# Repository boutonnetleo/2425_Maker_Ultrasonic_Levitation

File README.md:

# 2425_Maker_Ultrasonic_Levitation
Ultrasonic levitation using phased array

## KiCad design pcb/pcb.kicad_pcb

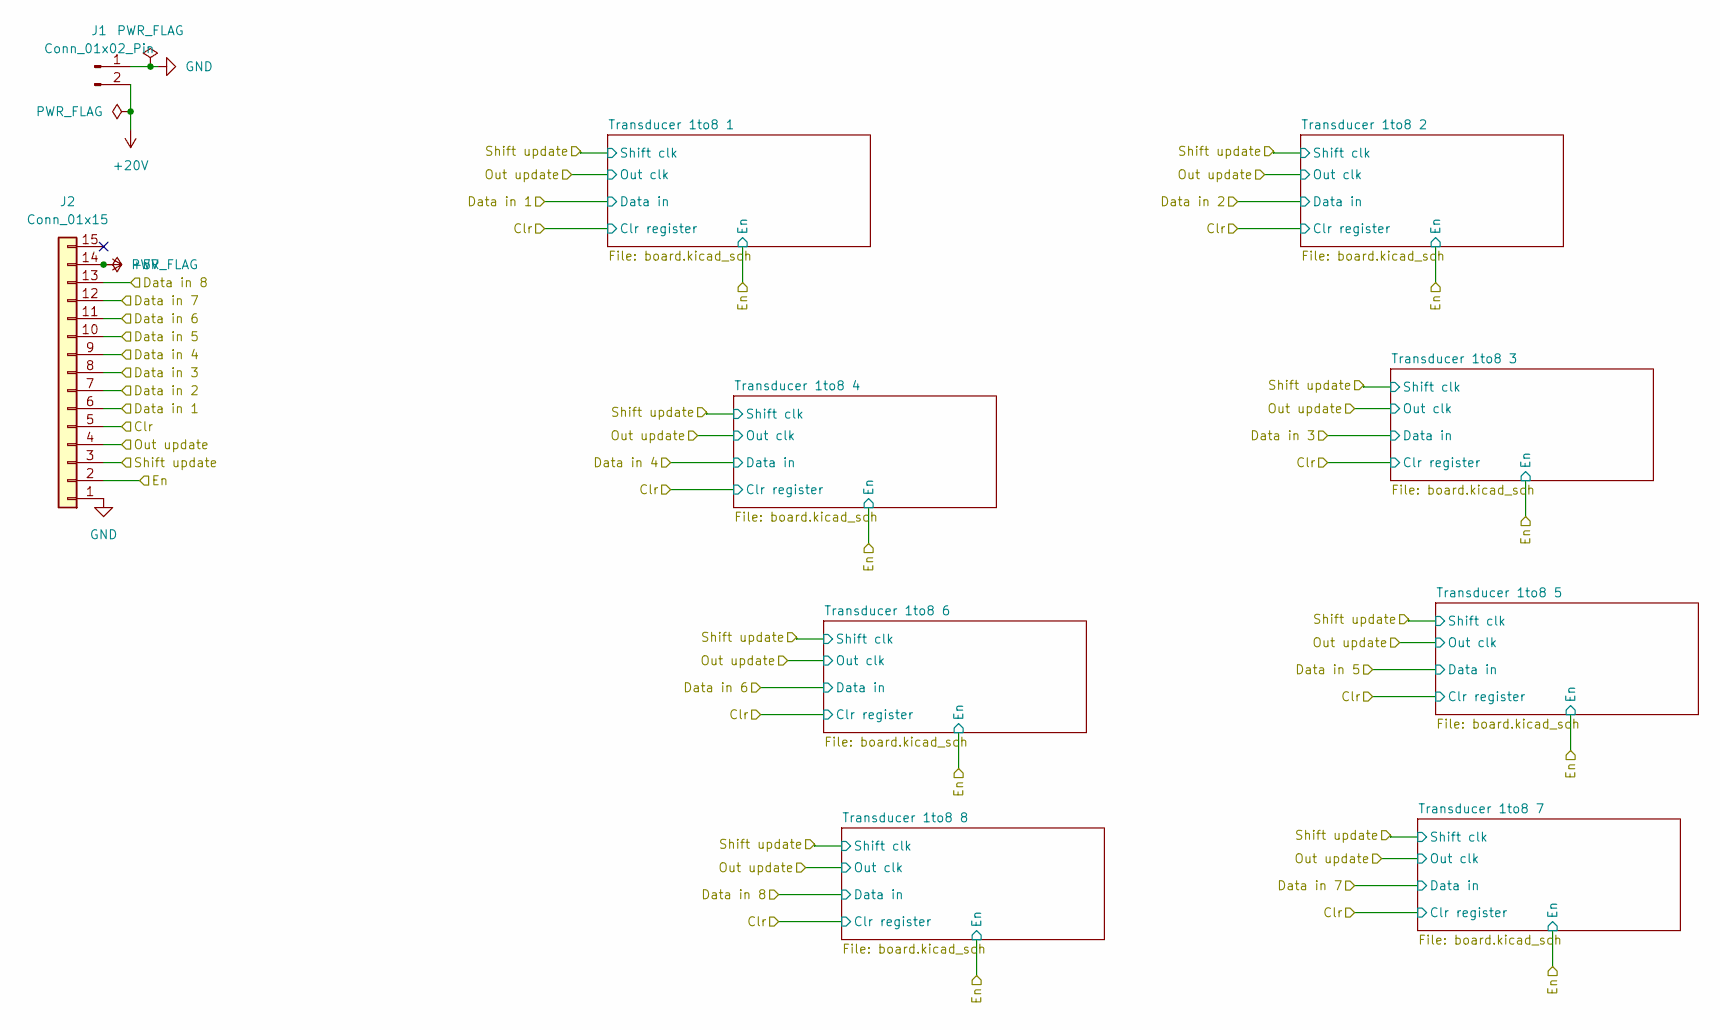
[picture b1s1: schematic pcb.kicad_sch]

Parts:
J1: Conn_01x02_Pin; AMASS_XT30UPB-F_1x02_P5.0mm_Vertical; JLCPCB C428721
J2: Conn_01x15; PinHeader_1x15_P2.54mm_Vertical; JLCPCB C7509525

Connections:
+5V: J2.14; also elsewhere on the board
+20V: J1.2; also elsewhere on the board
/Clr: J2.5; also elsewhere on the board
/Data in 1: J2.6; also elsewhere on the board
/Data in 2: J2.7; also elsewhere on the board
/Data in 3: J2.8; also elsewhere on the board
/Data in 4: J2.9; also elsewhere on the board
/Data in 5: J2.10; also elsewhere on the board
/Data in 6: J2.11; also elsewhere on the board
/Data in 7: J2.12; also elsewhere on the board
/Data in 8: J2.13; also elsewhere on the board
/En: J2.2; also elsewhere on the board
/Out update: J2.4; also elsewhere on the board
/Shift update: J2.3; also elsewhere on the board
GND: J1.1, J2.1; also elsewhere on the board

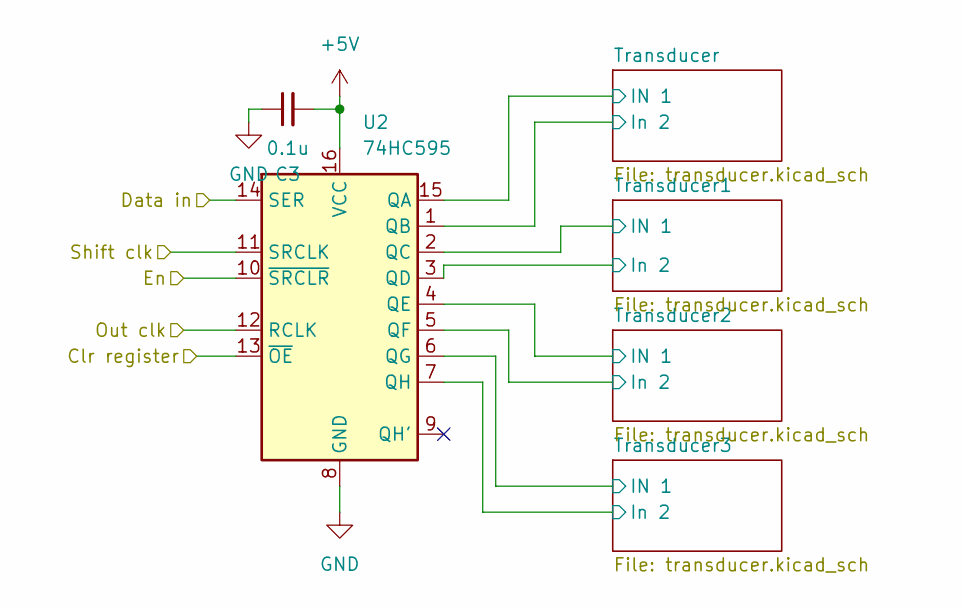
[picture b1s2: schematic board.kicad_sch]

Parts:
C3: 0.1u; C_0201_0603Metric; JLCPCB C386070
U2: 74HC595; SOIC-16_3.9x9.9mm_P1.27mm; JLCPCB C5947

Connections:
+5V: C3.2, U2.16 (VCC); also elsewhere on the board
/Clr: U2.13 (~OE); also elsewhere on the board
/Data in 1: U2.14 (SER); also elsewhere on the board
/En: U2.10 (~SRCLR); also elsewhere on the board
/Out update: U2.12 (RCLK); also elsewhere on the board
/Shift update: U2.11 (SRCLK); also elsewhere on the board
/Transducer 1to8 1/Transducer1/IN 1: U2.2 (QC); also elsewhere on the board
/Transducer 1to8 1/Transducer1/In 2: U2.3 (QD); also elsewhere on the board
/Transducer 1to8 1/Transducer2/IN 1: U2.4 (QE); also elsewhere on the board
/Transducer 1to8 1/Transducer2/In 2: U2.5 (QF); also elsewhere on the board
/Transducer 1to8 1/Transducer3/IN 1: U2.6 (QG); also elsewhere on the board
/Transducer 1to8 1/Transducer3/In 2: U2.7 (QH); also elsewhere on the board
/Transducer 1to8 1/Transducer/IN 1: U2.15 (QA); also elsewhere on the board
/Transducer 1to8 1/Transducer/In 2: U2.1 (QB); also elsewhere on the board
GND: C3.1, U2.8 (GND); also elsewhere on the board

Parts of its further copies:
C10, C19, C28, C37, C46, C55, C64: 0.1u; C_0201_0603Metric; JLCPCB C386070
U6, U11, U16, U21, U26, U31, U36: 74HC595; SOIC-16_3.9x9.9mm_P1.27mm; JLCPCB C5947

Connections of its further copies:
+5V: C10.2, C19.2, C28.2, C37.2, C46.2, C55.2, C64.2, U6.16 (VCC), U11.16 (VCC), U16.16 (VCC), U21.16 (VCC), U26.16 (VCC), U31.16 (VCC), U36.16 (VCC); also elsewhere on the board
/Clr: U6.13 (~OE), U11.13 (~OE), U16.13 (~OE), U21.13 (~OE), U26.13 (~OE), U31.13 (~OE), U36.13 (~OE); also elsewhere on the board
/Data in 2: U6.14 (SER); also elsewhere on the board
/Data in 3: U11.14 (SER); also elsewhere on the board
/Data in 4: U16.14 (SER); also elsewhere on the board
/Data in 5: U21.14 (SER); also elsewhere on the board
/Data in 6: U26.14 (SER); also elsewhere on the board
/Data in 7: U31.14 (SER); also elsewhere on the board
/Data in 8: U36.14 (SER); also elsewhere on the board
/En: U6.10 (~SRCLR), U11.10 (~SRCLR), U16.10 (~SRCLR), U21.10 (~SRCLR), U26.10 (~SRCLR), U31.10 (~SRCLR), U36.10 (~SRCLR); also elsewhere on the board
/Out update: U6.12 (RCLK), U11.12 (RCLK), U16.12 (RCLK), U21.12 (RCLK), U26.12 (RCLK), U31.12 (RCLK), U36.12 (RCLK); also elsewhere on the board
/Shift update: U6.11 (SRCLK), U11.11 (SRCLK), U16.11 (SRCLK), U21.11 (SRCLK), U26.11 (SRCLK), U31.11 (SRCLK), U36.11 (SRCLK); also elsewhere on the board
/Transducer 1to8 2/Transducer1/IN 1: U6.2 (QC); also elsewhere on the board
/Transducer 1to8 2/Transducer1/In 2: U6.3 (QD); also elsewhere on the board
/Transducer 1to8 2/Transducer2/IN 1: U6.4 (QE); also elsewhere on the board
/Transducer 1to8 2/Transducer2/In 2: U6.5 (QF); also elsewhere on the board
/Transducer 1to8 2/Transducer3/IN 1: U6.6 (QG); also elsewhere on the board
/Transducer 1to8 2/Transducer3/In 2: U6.7 (QH); also elsewhere on the board
/Transducer 1to8 2/Transducer/IN 1: U6.15 (QA); also elsewhere on the board
/Transducer 1to8 2/Transducer/In 2: U6.1 (QB); also elsewhere on the board
/Transducer 1to8 3/Transducer1/IN 1: U11.2 (QC); also elsewhere on the board
/Transducer 1to8 3/Transducer1/In 2: U11.3 (QD); also elsewhere on the board
/Transducer 1to8 3/Transducer2/IN 1: U11.4 (QE); also elsewhere on the board
/Transducer 1to8 3/Transducer2/In 2: U11.5 (QF); also elsewhere on the board
/Transducer 1to8 3/Transducer3/IN 1: U11.6 (QG); also elsewhere on the board
/Transducer 1to8 3/Transducer3/In 2: U11.7 (QH); also elsewhere on the board
/Transducer 1to8 3/Transducer/IN 1: U11.15 (QA); also elsewhere on the board
/Transducer 1to8 3/Transducer/In 2: U11.1 (QB); also elsewhere on the board
/Transducer 1to8 4/Transducer1/IN 1: U16.2 (QC); also elsewhere on the board
/Transducer 1to8 4/Transducer1/In 2: U16.3 (QD); also elsewhere on the board
/Transducer 1to8 4/Transducer2/IN 1: U16.4 (QE); also elsewhere on the board
/Transducer 1to8 4/Transducer2/In 2: U16.5 (QF); also elsewhere on the board
/Transducer 1to8 4/Transducer3/IN 1: U16.6 (QG); also elsewhere on the board
/Transducer 1to8 4/Transducer3/In 2: U16.7 (QH); also elsewhere on the board
/Transducer 1to8 4/Transducer/IN 1: U16.15 (QA); also elsewhere on the board
/Transducer 1to8 4/Transducer/In 2: U16.1 (QB); also elsewhere on the board
/Transducer 1to8 5/Transducer1/IN 1: U21.2 (QC); also elsewhere on the board
/Transducer 1to8 5/Transducer1/In 2: U21.3 (QD); also elsewhere on the board
/Transducer 1to8 5/Transducer2/IN 1: U21.4 (QE); also elsewhere on the board
/Transducer 1to8 5/Transducer2/In 2: U21.5 (QF); also elsewhere on the board
/Transducer 1to8 5/Transducer3/IN 1: U21.6 (QG); also elsewhere on the board
/Transducer 1to8 5/Transducer3/In 2: U21.7 (QH); also elsewhere on the board
/Transducer 1to8 5/Transducer/IN 1: U21.15 (QA); also elsewhere on the board
/Transducer 1to8 5/Transducer/In 2: U21.1 (QB); also elsewhere on the board
/Transducer 1to8 6/Transducer1/IN 1: U26.2 (QC); also elsewhere on the board
/Transducer 1to8 6/Transducer1/In 2: U26.3 (QD); also elsewhere on the board
/Transducer 1to8 6/Transducer2/IN 1: U26.4 (QE); also elsewhere on the board
/Transducer 1to8 6/Transducer2/In 2: U26.5 (QF); also elsewhere on the board
/Transducer 1to8 6/Transducer3/IN 1: U26.6 (QG); also elsewhere on the board
/Transducer 1to8 6/Transducer3/In 2: U26.7 (QH); also elsewhere on the board
/Transducer 1to8 6/Transducer/IN 1: U26.15 (QA); also elsewhere on the board
/Transducer 1to8 6/Transducer/In 2: U26.1 (QB); also elsewhere on the board
/Transducer 1to8 7/Transducer1/IN 1: U31.2 (QC); also elsewhere on the board
/Transducer 1to8 7/Transducer1/In 2: U31.3 (QD); also elsewhere on the board
/Transducer 1to8 7/Transducer2/IN 1: U31.4 (QE); also elsewhere on the board
/Transducer 1to8 7/Transducer2/In 2: U31.5 (QF); also elsewhere on the board
/Transducer 1to8 7/Transducer3/IN 1: U31.6 (QG); also elsewhere on the board
/Transducer 1to8 7/Transducer3/In 2: U31.7 (QH); also elsewhere on the board
/Transducer 1to8 7/Transducer/IN 1: U31.15 (QA); also elsewhere on the board
/Transducer 1to8 7/Transducer/In 2: U31.1 (QB); also elsewhere on the board
/Transducer 1to8 8/Transducer1/IN 1: U36.2 (QC); also elsewhere on the board
/Transducer 1to8 8/Transducer1/In 2: U36.3 (QD); also elsewhere on the board
/Transducer 1to8 8/Transducer2/IN 1: U36.4 (QE); also elsewhere on the board
/Transducer 1to8 8/Transducer2/In 2: U36.5 (QF); also elsewhere on the board
/Transducer 1to8 8/Transducer3/IN 1: U36.6 (QG); also elsewhere on the board
/Transducer 1to8 8/Transducer3/In 2: U36.7 (QH); also elsewhere on the board
/Transducer 1to8 8/Transducer/IN 1: U36.15 (QA); also elsewhere on the board
/Transducer 1to8 8/Transducer/In 2: U36.1 (QB); also elsewhere on the board
GND: C10.1, C19.1, C28.1, C37.1, C46.1, C55.1, C64.1, U6.8 (GND), U11.8 (GND), U16.8 (GND), U21.8 (GND), U26.8 (GND), U31.8 (GND), U36.8 (GND); also elsewhere on the board

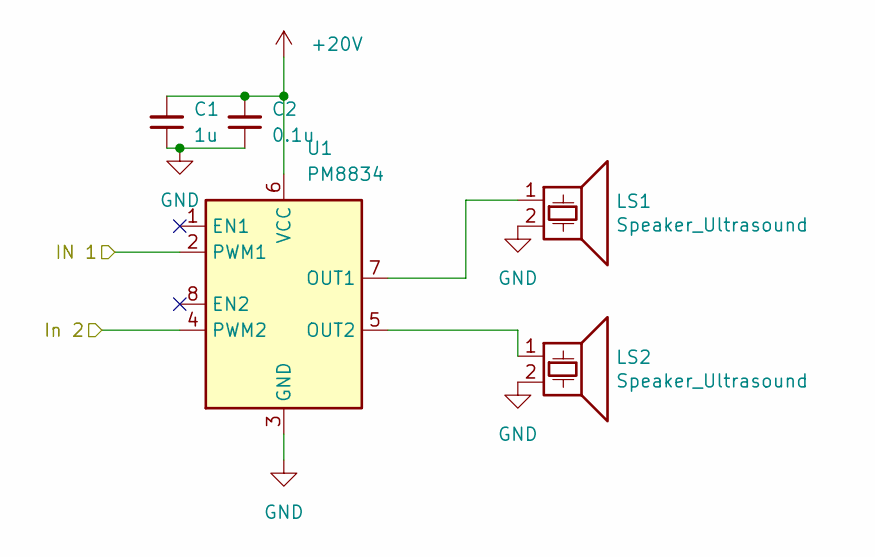
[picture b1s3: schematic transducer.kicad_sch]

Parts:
C1: 1u; C_0402_1005Metric; JLCPCB C52923
C2: 0.1u; C_0201_0603Metric; JLCPCB C386070
LS1, LS2: Speaker_Ultrasound; MSO-P1040H07T
U1: PM8834; SOIC-8_3.9x4.9mm_P1.27mm; JLCPCB C465729

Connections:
+20V: C1.2, C2.2, U1.6 (VCC); also elsewhere on the board
/Transducer 1to8 1/Transducer/IN 1: U1.2 (PWM1); also elsewhere on the board
/Transducer 1to8 1/Transducer/In 2: U1.4 (PWM2); also elsewhere on the board
GND: C1.1, C2.1, LS1.2, LS2.2, U1.3 (GND); also elsewhere on the board
unnamed: LS1.1, U1.7 (OUT1)
unnamed: LS2.1, U1.5 (OUT2)

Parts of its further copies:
C4, C6, C8, C11, C13, C15, C17, C20, C22, C24, C26, C29, C31, C33, C35, C38, C40, C42, C44, C47, C49, C51, C53, C56, C58, C60, C62, C65, C67, C69, C71: 1u; C_0402_1005Metric; JLCPCB C52923
C5, C7, C9, C12, C14, C16, C18, C21, C23, C25, C27, C30, C32, C34, C36, C39, C41, C43, C45, C48, C50, C52, C54, C57, C59, C61, C63, C66, C68, C70, C72: 0.1u; C_0201_0603Metric; JLCPCB C386070
LS3, LS4, LS5, LS6, LS7, LS8, LS9, LS10, LS11, LS12, LS13, LS14, LS15, LS16, LS17, LS18, LS19, LS20, LS21, LS22, LS23, LS24, LS25, LS26, LS27, LS28, LS29, LS30, LS31, LS32, LS33, LS34, LS35, LS36, LS37, LS38, LS39, LS40, LS41, LS42, LS43, LS44, LS45, LS46, LS47, LS48, LS49, LS50, LS51, LS52, LS53, LS54, LS55, LS56, LS57, LS58, LS59, LS60, LS61, LS62, LS63, LS64: Speaker_Ultrasound; MSO-P1040H07T
U3, U4, U5, U7, U8, U9, U10, U12, U13, U14, U15, U17, U18, U19, U20, U22, U23, U24, U25, U27, U28, U29, U30, U32, U33, U34, U35, U37, U38, U39, U40: PM8834; SOIC-8_3.9x4.9mm_P1.27mm; JLCPCB C465729

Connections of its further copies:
+20V: C4.2, C5.2, C6.2, C7.2, C8.2, C9.2, C11.2, C12.2, C13.2, C14.2, C15.2, C16.2, C17.2, C18.2, C20.2, C21.2, C22.2, C23.2, C24.2, C25.2, C26.2, C27.2, C29.2, C30.2, C31.2, C32.2, C33.2, C34.2, C35.2, C36.2, C38.2, C39.2, C40.2, C41.2, C42.2, C43.2, C44.2, C45.2, C47.2, C48.2, C49.2, C50.2, C51.2, C52.2, C53.2, C54.2, C56.2, C57.2, C58.2, C59.2, C60.2, C61.2, C62.2, C63.2, C65.2, C66.2, C67.2, C68.2, C69.2, C70.2, C71.2, C72.2, U3.6 (VCC), U4.6 (VCC), U5.6 (VCC), U7.6 (VCC), U8.6 (VCC), U9.6 (VCC), U10.6 (VCC), U12.6 (VCC), U13.6 (VCC), U14.6 (VCC), U15.6 (VCC), U17.6 (VCC), U18.6 (VCC), U19.6 (VCC), U20.6 (VCC), U22.6 (VCC), U23.6 (VCC), U24.6 (VCC), U25.6 (VCC), U27.6 (VCC), U28.6 (VCC), U29.6 (VCC), U30.6 (VCC), U32.6 (VCC), U33.6 (VCC), U34.6 (VCC), U35.6 (VCC), U37.6 (VCC), U38.6 (VCC), U39.6 (VCC), U40.6 (VCC); also elsewhere on the board
/Transducer 1to8 1/Transducer1/IN 1: U3.2 (PWM1); also elsewhere on the board
/Transducer 1to8 1/Transducer1/In 2: U3.4 (PWM2); also elsewhere on the board
/Transducer 1to8 1/Transducer2/IN 1: U4.2 (PWM1); also elsewhere on the board
/Transducer 1to8 1/Transducer2/In 2: U4.4 (PWM2); also elsewhere on the board
/Transducer 1to8 1/Transducer3/IN 1: U5.2 (PWM1); also elsewhere on the board
/Transducer 1to8 1/Transducer3/In 2: U5.4 (PWM2); also elsewhere on the board
/Transducer 1to8 2/Transducer1/IN 1: U9.2 (PWM1); also elsewhere on the board
/Transducer 1to8 2/Transducer1/In 2: U9.4 (PWM2); also elsewhere on the board
/Transducer 1to8 2/Transducer2/IN 1: U8.2 (PWM1); also elsewhere on the board
/Transducer 1to8 2/Transducer2/In 2: U8.4 (PWM2); also elsewhere on the board
/Transducer 1to8 2/Transducer3/IN 1: U7.2 (PWM1); also elsewhere on the board
/Transducer 1to8 2/Transducer3/In 2: U7.4 (PWM2); also elsewhere on the board
/Transducer 1to8 2/Transducer/IN 1: U10.2 (PWM1); also elsewhere on the board
/Transducer 1to8 2/Transducer/In 2: U10.4 (PWM2); also elsewhere on the board
/Transducer 1to8 3/Transducer1/IN 1: U14.2 (PWM1); also elsewhere on the board
/Transducer 1to8 3/Transducer1/In 2: U14.4 (PWM2); also elsewhere on the board
/Transducer 1to8 3/Transducer2/IN 1: U13.2 (PWM1); also elsewhere on the board
/Transducer 1to8 3/Transducer2/In 2: U13.4 (PWM2); also elsewhere on the board
/Transducer 1to8 3/Transducer3/IN 1: U12.2 (PWM1); also elsewhere on the board
/Transducer 1to8 3/Transducer3/In 2: U12.4 (PWM2); also elsewhere on the board
/Transducer 1to8 3/Transducer/IN 1: U15.2 (PWM1); also elsewhere on the board
/Transducer 1to8 3/Transducer/In 2: U15.4 (PWM2); also elsewhere on the board
/Transducer 1to8 4/Transducer1/IN 1: U19.2 (PWM1); also elsewhere on the board
/Transducer 1to8 4/Transducer1/In 2: U19.4 (PWM2); also elsewhere on the board
/Transducer 1to8 4/Transducer2/IN 1: U18.2 (PWM1); also elsewhere on the board
/Transducer 1to8 4/Transducer2/In 2: U18.4 (PWM2); also elsewhere on the board
/Transducer 1to8 4/Transducer3/IN 1: U17.2 (PWM1); also elsewhere on the board
/Transducer 1to8 4/Transducer3/In 2: U17.4 (PWM2); also elsewhere on the board
/Transducer 1to8 4/Transducer/IN 1: U20.2 (PWM1); also elsewhere on the board
/Transducer 1to8 4/Transducer/In 2: U20.4 (PWM2); also elsewhere on the board
/Transducer 1to8 5/Transducer1/IN 1: U24.2 (PWM1); also elsewhere on the board
/Transducer 1to8 5/Transducer1/In 2: U24.4 (PWM2); also elsewhere on the board
/Transducer 1to8 5/Transducer2/IN 1: U23.2 (PWM1); also elsewhere on the board
/Transducer 1to8 5/Transducer2/In 2: U23.4 (PWM2); also elsewhere on the board
/Transducer 1to8 5/Transducer3/IN 1: U22.2 (PWM1); also elsewhere on the board
/Transducer 1to8 5/Transducer3/In 2: U22.4 (PWM2); also elsewhere on the board
/Transducer 1to8 5/Transducer/IN 1: U25.2 (PWM1); also elsewhere on the board
/Transducer 1to8 5/Transducer/In 2: U25.4 (PWM2); also elsewhere on the board
/Transducer 1to8 6/Transducer1/IN 1: U29.2 (PWM1); also elsewhere on the board
/Transducer 1to8 6/Transducer1/In 2: U29.4 (PWM2); also elsewhere on the board
/Transducer 1to8 6/Transducer2/IN 1: U28.2 (PWM1); also elsewhere on the board
/Transducer 1to8 6/Transducer2/In 2: U28.4 (PWM2); also elsewhere on the board
/Transducer 1to8 6/Transducer3/IN 1: U27.2 (PWM1); also elsewhere on the board
/Transducer 1to8 6/Transducer3/In 2: U27.4 (PWM2); also elsewhere on the board
/Transducer 1to8 6/Transducer/IN 1: U30.2 (PWM1); also elsewhere on the board
/Transducer 1to8 6/Transducer/In 2: U30.4 (PWM2); also elsewhere on the board
/Transducer 1to8 7/Transducer1/IN 1: U34.2 (PWM1); also elsewhere on the board
/Transducer 1to8 7/Transducer1/In 2: U34.4 (PWM2); also elsewhere on the board
/Transducer 1to8 7/Transducer2/IN 1: U33.2 (PWM1); also elsewhere on the board
/Transducer 1to8 7/Transducer2/In 2: U33.4 (PWM2); also elsewhere on the board
/Transducer 1to8 7/Transducer3/IN 1: U32.2 (PWM1); also elsewhere on the board
/Transducer 1to8 7/Transducer3/In 2: U32.4 (PWM2); also elsewhere on the board
/Transducer 1to8 7/Transducer/IN 1: U35.2 (PWM1); also elsewhere on the board
/Transducer 1to8 7/Transducer/In 2: U35.4 (PWM2); also elsewhere on the board
/Transducer 1to8 8/Transducer1/IN 1: U39.2 (PWM1); also elsewhere on the board
/Transducer 1to8 8/Transducer1/In 2: U39.4 (PWM2); also elsewhere on the board
/Transducer 1to8 8/Transducer2/IN 1: U38.2 (PWM1); also elsewhere on the board
/Transducer 1to8 8/Transducer2/In 2: U38.4 (PWM2); also elsewhere on the board
/Transducer 1to8 8/Transducer3/IN 1: U37.2 (PWM1); also elsewhere on the board
/Transducer 1to8 8/Transducer3/In 2: U37.4 (PWM2); also elsewhere on the board
/Transducer 1to8 8/Transducer/IN 1: U40.2 (PWM1); also elsewhere on the board
/Transducer 1to8 8/Transducer/In 2: U40.4 (PWM2); also elsewhere on the board
GND: C4.1, C5.1, C6.1, C7.1, C8.1, C9.1, C11.1, C12.1, C13.1, C14.1, C15.1, C16.1, C17.1, C18.1, C20.1, C21.1, C22.1, C23.1, C24.1, C25.1, C26.1, C27.1, C29.1, C30.1, C31.1, C32.1, C33.1, C34.1, C35.1, C36.1, C38.1, C39.1, C40.1, C41.1, C42.1, C43.1, C44.1, C45.1, C47.1, C48.1, C49.1, C50.1, C51.1, C52.1, C53.1, C54.1, C56.1, C57.1, C58.1, C59.1, C60.1, C61.1, C62.1, C63.1, C65.1, C66.1, C67.1, C68.1, C69.1, C70.1, C71.1, C72.1, LS3.2, LS4.2, LS5.2, LS6.2, LS7.2, LS8.2, LS9.2, LS10.2, LS11.2, LS12.2, LS13.2, LS14.2, LS15.2, LS16.2, LS17.2, LS18.2, LS19.2, LS20.2, LS21.2, LS22.2, LS23.2, LS24.2, LS25.2, LS26.2, LS27.2, LS28.2, LS29.2, LS30.2, LS31.2, LS32.2, LS33.2, LS34.2, LS35.2, LS36.2, LS37.2, LS38.2, LS39.2, LS40.2, LS41.2, LS42.2, LS43.2, LS44.2, LS45.2, LS46.2, LS47.2, LS48.2, LS49.2, LS50.2, LS51.2, LS52.2, LS53.2, LS54.2, LS55.2, LS56.2, LS57.2, LS58.2, LS59.2, LS60.2, LS61.2, LS62.2, LS63.2, LS64.2, U3.3 (GND), U4.3 (GND), U5.3 (GND), U7.3 (GND), U8.3 (GND), U9.3 (GND), U10.3 (GND), U12.3 (GND), U13.3 (GND), U14.3 (GND), U15.3 (GND), U17.3 (GND), U18.3 (GND), U19.3 (GND), U20.3 (GND), U22.3 (GND), U23.3 (GND), U24.3 (GND), U25.3 (GND), U27.3 (GND), U28.3 (GND), U29.3 (GND), U30.3 (GND), U32.3 (GND), U33.3 (GND), U34.3 (GND), U35.3 (GND), U37.3 (GND), U38.3 (GND), U39.3 (GND), U40.3 (GND); also elsewhere on the board
unnamed: LS3.1, U3.7 (OUT1)
unnamed: LS4.1, U3.5 (OUT2)
unnamed: LS5.1, U4.7 (OUT1)
unnamed: LS6.1, U4.5 (OUT2)
unnamed: LS7.1, U5.7 (OUT1)
unnamed: LS8.1, U5.5 (OUT2)
unnamed: LS9.1, U7.7 (OUT1)
unnamed: LS10.1, U7.5 (OUT2)
unnamed: LS11.1, U8.7 (OUT1)
unnamed: LS12.1, U8.5 (OUT2)
unnamed: LS13.1, U9.7 (OUT1)
unnamed: LS14.1, U9.5 (OUT2)
unnamed: LS15.1, U10.7 (OUT1)
unnamed: LS16.1, U10.5 (OUT2)
unnamed: LS17.1, U12.7 (OUT1)
unnamed: LS18.1, U12.5 (OUT2)
unnamed: LS19.1, U13.7 (OUT1)
unnamed: LS20.1, U13.5 (OUT2)
unnamed: LS21.1, U14.7 (OUT1)
unnamed: LS22.1, U14.5 (OUT2)
unnamed: LS23.1, U15.7 (OUT1)
unnamed: LS24.1, U15.5 (OUT2)
unnamed: LS25.1, U17.7 (OUT1)
unnamed: LS26.1, U17.5 (OUT2)
unnamed: LS27.1, U18.7 (OUT1)
unnamed: LS28.1, U18.5 (OUT2)
unnamed: LS29.1, U19.7 (OUT1)
unnamed: LS30.1, U19.5 (OUT2)
unnamed: LS31.1, U20.7 (OUT1)
unnamed: LS32.1, U20.5 (OUT2)
unnamed: LS33.1, U22.7 (OUT1)
unnamed: LS34.1, U22.5 (OUT2)
unnamed: LS35.1, U23.7 (OUT1)
unnamed: LS36.1, U23.5 (OUT2)
unnamed: LS37.1, U24.7 (OUT1)
unnamed: LS38.1, U24.5 (OUT2)
unnamed: LS39.1, U25.7 (OUT1)
unnamed: LS40.1, U25.5 (OUT2)
unnamed: LS41.1, U27.7 (OUT1)
unnamed: LS42.1, U27.5 (OUT2)
unnamed: LS43.1, U28.7 (OUT1)
unnamed: LS44.1, U28.5 (OUT2)
unnamed: LS45.1, U29.7 (OUT1)
unnamed: LS46.1, U29.5 (OUT2)
unnamed: LS47.1, U30.7 (OUT1)
unnamed: LS48.1, U30.5 (OUT2)
unnamed: LS49.1, U32.7 (OUT1)
unnamed: LS50.1, U32.5 (OUT2)
unnamed: LS51.1, U33.7 (OUT1)
unnamed: LS52.1, U33.5 (OUT2)
unnamed: LS53.1, U34.7 (OUT1)
unnamed: LS54.1, U34.5 (OUT2)
unnamed: LS55.1, U35.7 (OUT1)
unnamed: LS56.1, U35.5 (OUT2)
unnamed: LS57.1, U37.7 (OUT1)
unnamed: LS58.1, U37.5 (OUT2)
unnamed: LS59.1, U38.7 (OUT1)
unnamed: LS60.1, U38.5 (OUT2)
unnamed: LS61.1, U39.7 (OUT1)
unnamed: LS62.1, U39.5 (OUT2)
unnamed: LS63.1, U40.7 (OUT1)
unnamed: LS64.1, U40.5 (OUT2)

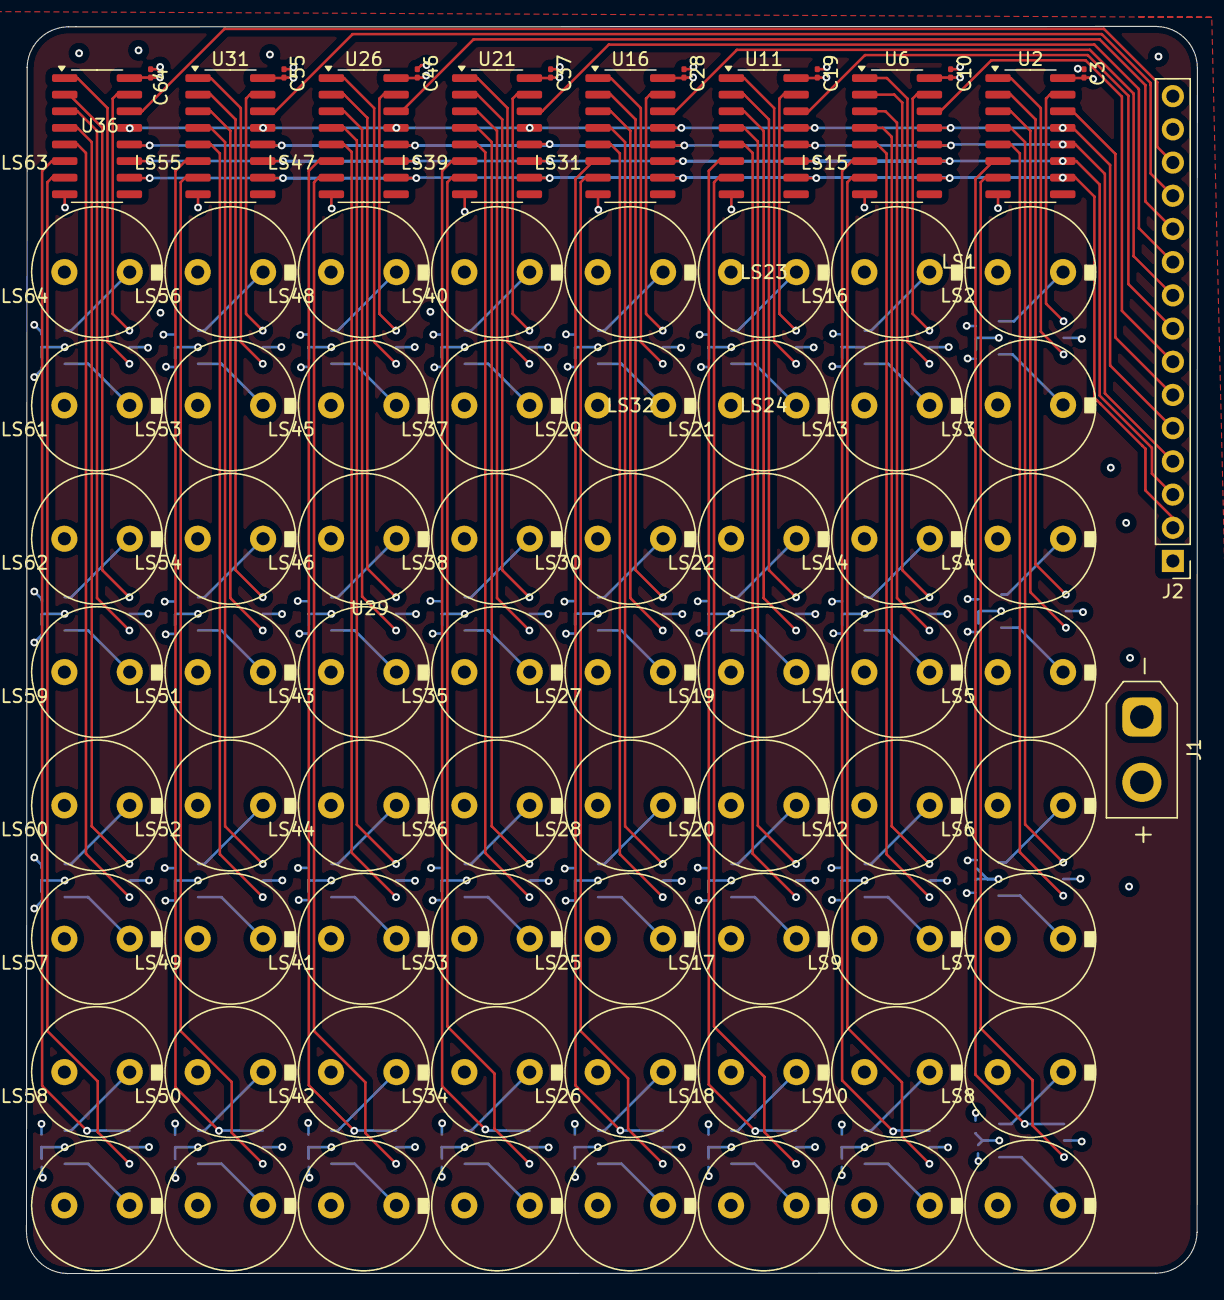
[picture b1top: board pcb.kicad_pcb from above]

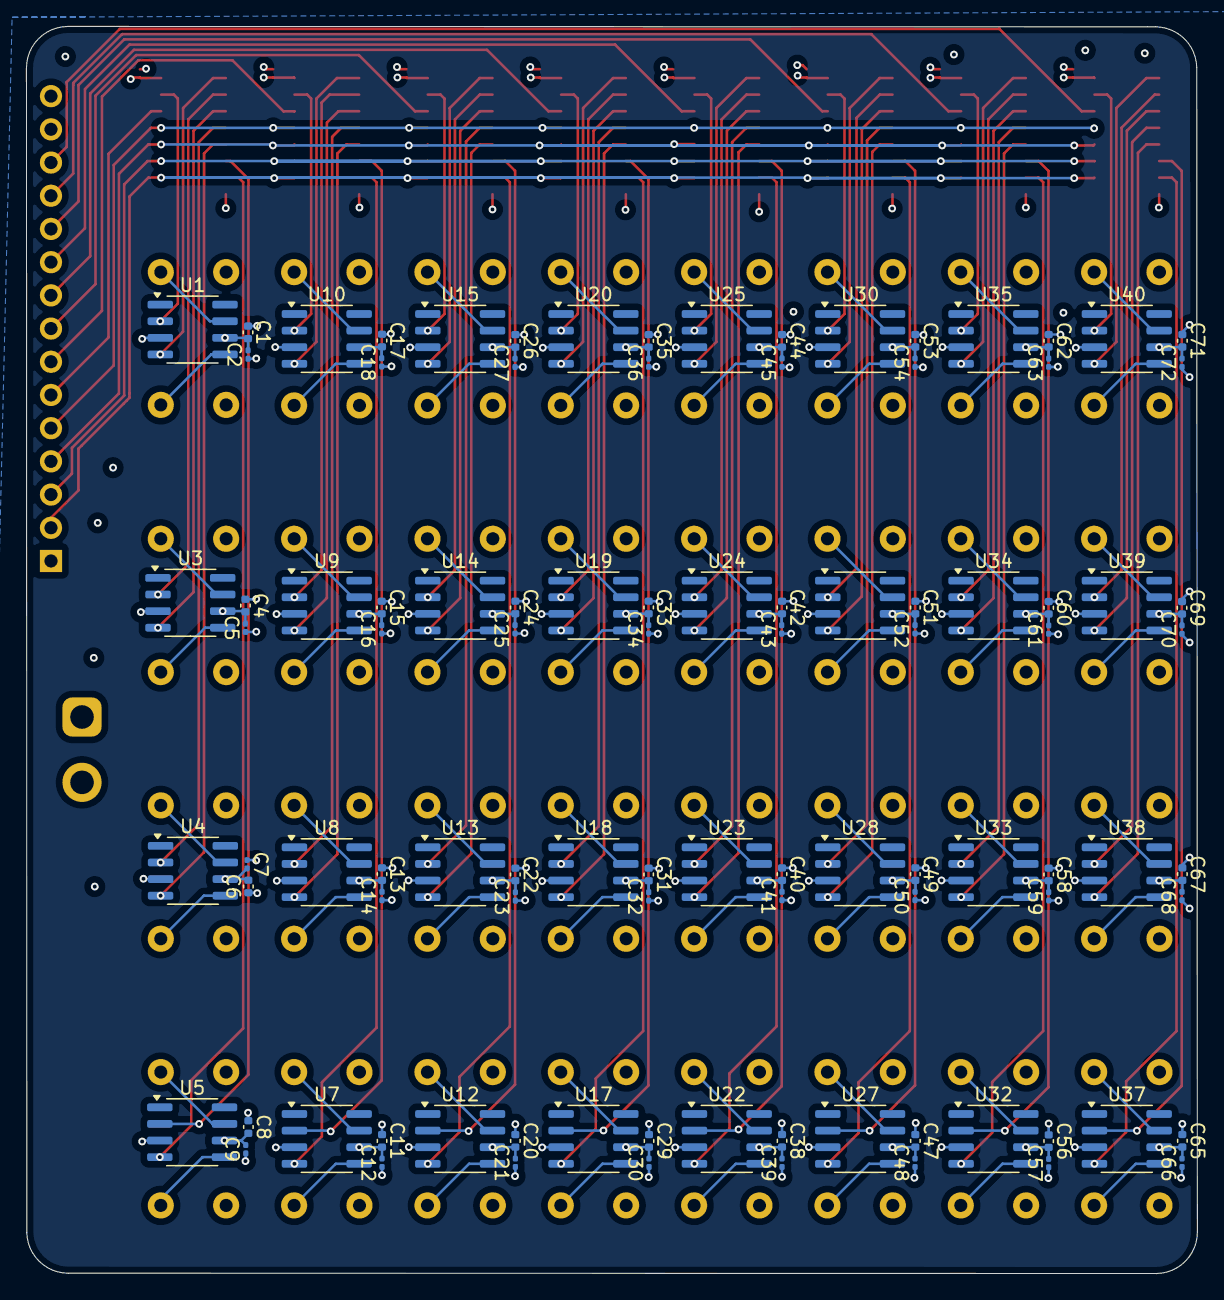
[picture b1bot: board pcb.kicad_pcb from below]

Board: 4 copper layers, 89.6 x 95.4 mm, 178 parts (96 on the bottom side), 143 nets.

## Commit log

2025-04-26 Pcb du projet (pas fini)
    Pcb qui aurait dû être transmis si je l'avais fini à temps
2025-04-27 ajout images
